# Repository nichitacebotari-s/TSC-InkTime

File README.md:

# TSC-InkTime
InkTime is a time-first smartwatch optimized for month-class battery life and sunlight readability.

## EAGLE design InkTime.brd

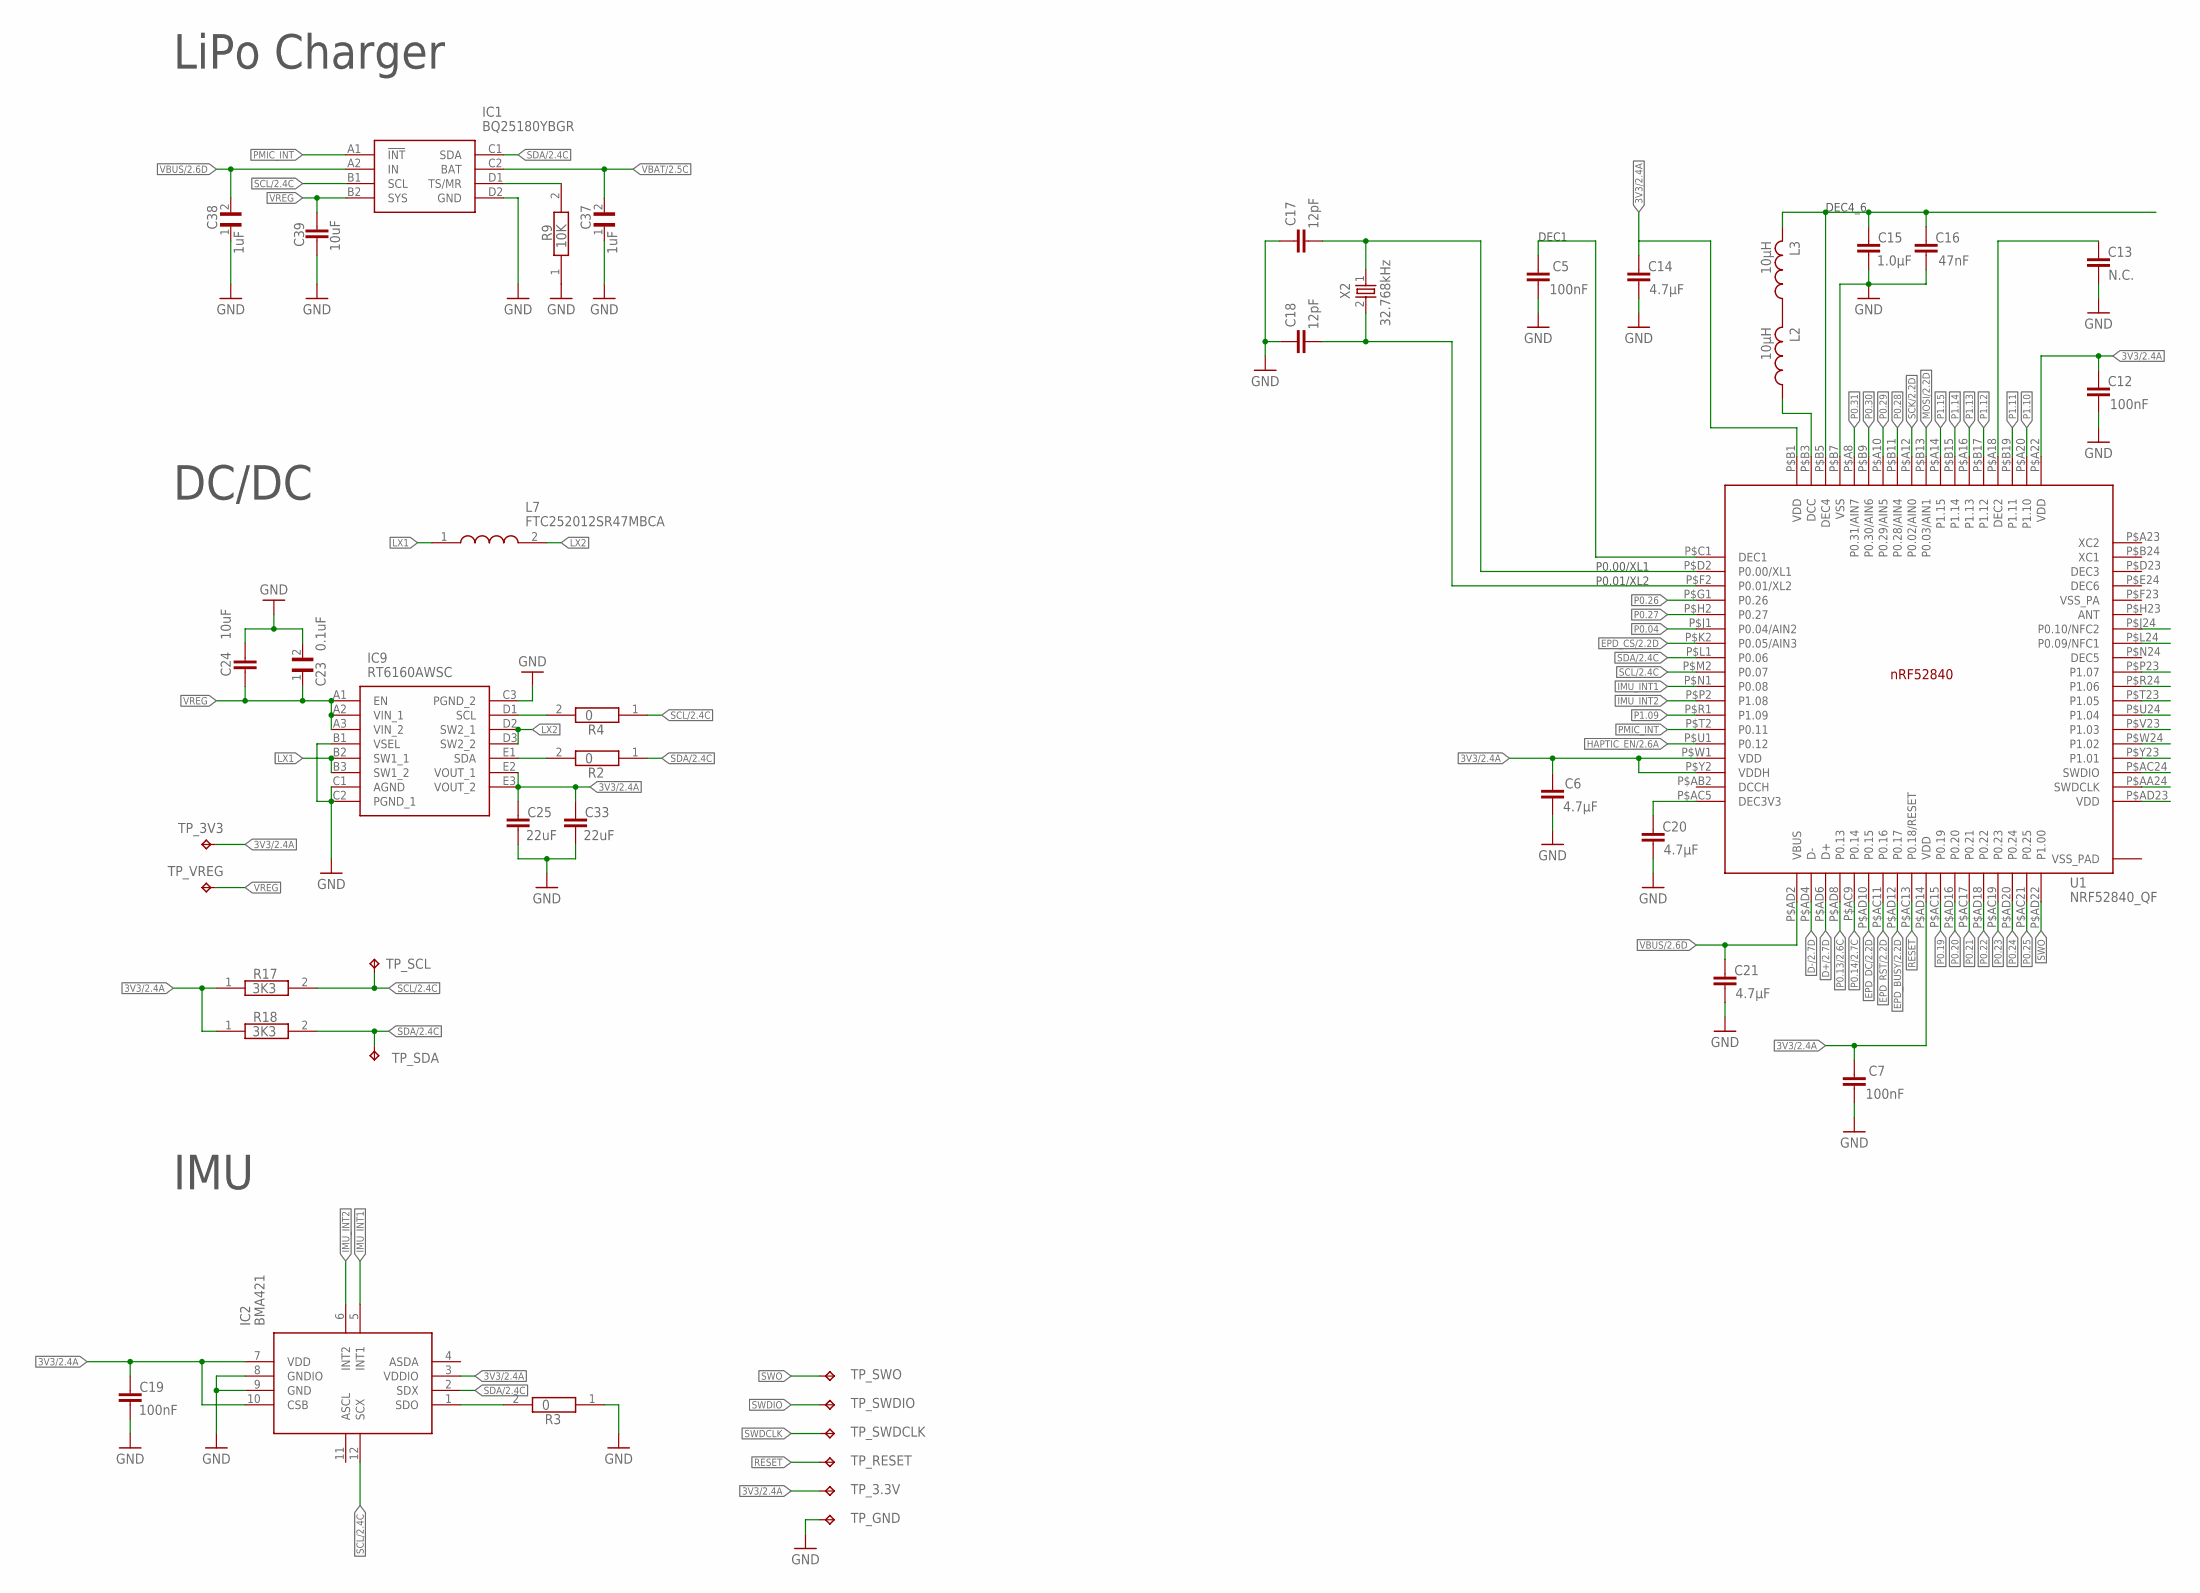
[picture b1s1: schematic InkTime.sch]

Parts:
C5, C7, C12, C19: 100nF; NORDIC_NRF_3_RESC0201_L
C6, C14, C20, C21: 4.7μF; NORDIC_NRF_3_RESC0201_L
C13: N.C.; NORDIC_NRF_3_RESC0201_L
C15: 1.0μF; NORDIC_NRF_3_RESC0201_L
C16: 47nF; NORDIC_NRF_3_RESC0201_L
C17, C18: 12pF; NORDIC_NRF_3_RESC0201_L
C23: 0.1uF; GRM011R60J152KE01L_2_CAPC0201X13N
C24, C39: 10uF; NORDIC_NRF_3_RESC0201_L
C25, C33: 22uF; NORDIC_NRF_3_RESC0201_L
C37, C38: 1uF; GRM011R60J152KE01L_2_CAPC0201X13N
IC1: BQ25180YBGR; BQ25180YBGR_BGA8C40P2X4_100X155X50
IC2: BMA421; BMA423_BMA423
IC9: RT6160AWSC; RT6160AWSC_BGA15C40P3X5_140X230X60
L2, L3: 10μH; NORDIC_NRF_2_RESC0402_L
L7: FTC252012SR47MBCA; MLP2016SR47MT0S1_INDC2016X100N
R2, R3, R4: 0; ERA-1AEB3401C_0201
R9: 10K; ERA-1AEB3401C_0201
R17, R18: 3K3; ERA-1AEB3401C_0201
TP_3.3V, TP_3V3: HECTOR_WATCH_1_TPTP20R; HECTOR_WATCH_1_TP20R
TP_GND: HECTOR_WATCH_1_TPTP20R; HECTOR_WATCH_1_TP20R
TP_RESET: HECTOR_WATCH_1_TPTP20R; HECTOR_WATCH_1_TP20R
TP_SCL: HECTOR_WATCH_1_TPTP20R; HECTOR_WATCH_1_TP20R
TP_SDA: HECTOR_WATCH_1_TPTP20R; HECTOR_WATCH_1_TP20R
TP_SWDCLK: HECTOR_WATCH_1_TPTP20R; HECTOR_WATCH_1_TP20R
TP_SWDIO: HECTOR_WATCH_1_TPTP20R; HECTOR_WATCH_1_TP20R
TP_SWO: HECTOR_WATCH_1_TPTP20R; HECTOR_WATCH_1_TP20R
TP_VREG: HECTOR_WATCH_1_TPTP20R; HECTOR_WATCH_1_TP20R
U1: NRF52840_QF; NORDIC_NRF_4_AQFN50P700X700X85_HS-74N
X2: 32.768kHz; NORDIC_NRF_1_XTAL_3215_N

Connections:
3V3/2.4A: C25.1, C33.1, IC9.E2 (VOUT_1), IC9.E3 (VOUT_2)
D+/2.7D: U1.P$AD6 (D+)
D-/2.7D: U1.P$AD4 (D-)
EPD_BUSY/2.2D: U1.P$AD12 (P0.17)
EPD_CS/2.2D: U1.P$K2 (P0.05/AIN3)
EPD_DC/2.2D: U1.P$AD10 (P0.15)
EPD_RST/2.2D: U1.P$AC11 (P0.16)
GND: C5.2, C6.2, C7.2, C12.2, C13.2, C14.2, C15.2, C16.2, C17.1, C18.1, C19.2, C20.2, C21.2, C23.2, C24.1, C25.2, C33.2, C37.1, C38.1, C39.2, IC1.D2 (GND), IC2.8 (GNDIO), IC2.9 (GND), IC9.C3 (PGND_2), R3.1, R9.1, TP_GND.TP, U1.P$B7 (VSS)
HAPTIC_EN/2.6A: U1.P$U1 (P0.12)
IMU_INT1: IC2.5 (INT1)
IMU_INT2: IC2.6 (INT2)
LX1: L7.1
LX2: L7.2
MOSI/2.2D: U1.P$B13 (P0.03/AIN1)
unnamed: IC1.D1 (TS/MR), R9.2
unnamed: IC9.D2 (SW2_1), IC9.D3 (SW2_2)
unnamed: IC9.D1 (SCL), R4.2
unnamed: IC9.E1 (SDA), R2.2
unnamed: C23.1, C24.2, IC9.A1 (EN), IC9.A2 (VIN_1), IC9.A3 (VIN_2)
unnamed: IC9.B2 (SW1_1), IC9.B3 (SW1_2)
unnamed: IC9.B1 (VSEL), IC9.C1 (AGND), IC9.C2 (PGND_1)
unnamed: R17.1, R18.1
unnamed: R17.2, TP_SCL.TP
unnamed: R18.2, TP_SDA.TP
unnamed: C21.1, U1.P$AD2 (VBUS)
unnamed: C7.1, U1.P$AD14 (VDD)
unnamed: C19.1, IC2.7 (VDD), IC2.10 (CSB)
unnamed: IC2.1 (SDO), R3.2
unnamed: C6.1, U1.P$W1 (VDD), U1.P$Y2 (VDDH)
unnamed: C20.1, U1.P$AC5 (DEC3V3)
unnamed: C5.1, U1.P$C1 (DEC1)
unnamed: C17.2, U1.P$D2 (P0.00/XL1), X2.1
unnamed: C18.2, U1.P$F2 (P0.01/XL2), X2.2
unnamed: C14.1, U1.P$B1 (VDD)
unnamed: C12.1, U1.P$A22 (VDD)
unnamed: C13.1, U1.P$A18 (DEC2)
unnamed: L2.1, U1.P$B3 (DCC)
unnamed: L2.2, L3.1
unnamed: C15.1, C16.1, L3.2, U1.P$B5 (DEC4)
P0.04: U1.P$J1 (P0.04/AIN2)
P0.13/2.6C: U1.P$AD8 (P0.13)
P0.14/2.7C: U1.P$AC9 (P0.14)
P0.19: U1.P$AC15 (P0.19)
P0.20: U1.P$AD16 (P0.20)
P0.21: U1.P$AC17 (P0.21)
P0.22: U1.P$AD18 (P0.22)
P0.23: U1.P$AC19 (P0.23)
P0.24: U1.P$AD20 (P0.24)
P0.25: U1.P$AC21 (P0.25)
P0.26: U1.P$G1 (P0.26)
P0.27: U1.P$H2 (P0.27)
P0.28: U1.P$B11 (P0.28/AIN4)
P0.29: U1.P$A10 (P0.29/AIN5)
P0.30: U1.P$B9 (P0.30/AIN6)
P0.31: U1.P$A8 (P0.31/AIN7)
P1.09: U1.P$R1 (P1.09)
P1.10: U1.P$A20 (P1.10)
P1.11: U1.P$B19 (P1.11)
P1.12: U1.P$B17 (P1.12)
P1.13: U1.P$A16 (P1.13)
P1.14: U1.P$B15 (P1.14)
P1.15: U1.P$A14 (P1.15)
PMIC_INT: IC1.A1 (!INT)
RESET: TP_RESET.TP
SCK/2.2D: U1.P$A12 (P0.02/AIN0)
SCL/2.4C: IC1.B1 (SCL)
SDA/2.4C: IC1.C1 (SDA)
SWDCLK: TP_SWDCLK.TP
SWDIO: TP_SWDIO.TP
SWO: TP_SWO.TP
VBAT/2.5C: C37.2, IC1.C2 (BAT)
VBUS/2.6D: C38.2, IC1.A2 (IN)
VREG: C39.1, IC1.B2 (SYS)

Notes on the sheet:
LiPo Charger
DC/DC
IMU
DEC1
P0.00/XL1
P0.01/XL2
DEC4_6

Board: 2 copper layers, 44 parts (0 on the bottom side), 30 nets, no tracks yet.

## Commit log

2026-04-10 Create a
2026-04-10 Create b
2026-04-10 Create c
2026-04-10 Create d
2026-04-10 Create LICENSE
2026-04-10 Rename b to sampe
2026-04-10 Rename sampe to sample
2026-04-10 Rename c to sample
2026-04-10 Create sample
